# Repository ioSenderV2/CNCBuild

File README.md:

# CNCBuild

The machine, and everything about building, wiring, configuring and instrumenting it. Gantry beams are
**stacked pairs of 8020 `30-6060`** on HGR20 rails and 1605 ball screws.

Written down because these facts kept getting re-derived in conversation - travels, plate dimensions,
what shares a drag chain, which stored setting disagreed with the machine. A firmware fork's scratch
folder was the wrong home for them. The project's history at milestone level is
[TIMELINE.md](TIMELINE.md).

| Folder | What is in it |
|---|---|
| [`machine/`](machine) | The build itself: extrusions, rails, screws, plates, and the mechanical decisions with their reasons |
| [`linear-encoder/`](linear-encoder) | Magnetic linear scales + AS5311 + ESP32-S3 → CAN → grblHAL. The most developed subsystem; design complete, nothing built |
| [`commissioning/`](commissioning) | Measurements taken **from the machine** - travels, squaring, tape extents. The authority when the config disagrees |
| [`wiring/`](wiring) | How the boxes connect - the DB37 between the controller box and the remote axis breakout box |

## Generated views - regenerate, never edit

Three files are built from the prose rather than maintained beside it, because a
hand-maintained summary drifts from what it summarises. That is not hypothetical here: on
2026-10-02 two settled decisions were relitigated, both because a pointer had gone stale.

| Build it with | What you get |
|---|---|
| **`tools\regen.ps1`** | **everything derived, in dependency order, ending with `CNC Build.zip`.** The registry check first, then VALUES/registry.html/fusion CSV, fasteners, the cut list, the 3D model, the shop pack tallies, STATUS and INDEX, the four checkers, then the PDFs - and `make-pdf` bundles the zip on a clean print. `-NoPdf` stops after the checkers and says plainly that the PDFs and the zip are then stale. **This is the one to run**; the rows below are what it calls |
| `python tools/status.py all` | [`STATUS.md`](STATUS.md) - every open item, harvested from the SETTLED: OPEN: FLAG: REJECTED: markers in the prose. [`INDEX.md`](INDEX.md) - every heading in the repo |
| `tools\make-pdf.ps1` | **`docs/build-document.pdf`** - the whole mechanical design as one printable file: the thirteen `machine/*.md` files in reading order, a clickable contents, all fifteen photographs embedded with their captions, and links into the shop pack. ~4.4 MB, 97 pages. **Untracked** - rebuild it, do not commit it |

**If a generated file and a `.md` file disagree, the `.md` file wins** and the generated copy
is stale. The PDF needs two packages - `python -m pip install markdown pillow` - the first to
render the prose, the second to scale the photographs to print size on the way in (22.9 MB of
originals become 4.4 MB of PDF, still over 300 dpi at the size they are printed; the originals
in `machine/photos/` are never touched). `status.py` is stdlib-only on purpose, because it
gates correctness and the PDF does not.

## What lives elsewhere

| | Where | Why |
|---|---|---|
| grblHAL firmware + the CAN plugin | `stevenrwood/iMXRT1062`, branch `srw/local-build-config` | It is firmware and needs that build tree |
| ioSender (the sender application) | `ioSenderV2/ioSender` | Its own product |

## A standing rule for this repo

**The machine is the authority, not the configuration.** `$130` once read 889 mm against a real 860 mm,
because a catalog preset overwrote a measured value - which quietly cost soft-limit protection until it
was found by accident. Anything in `commissioning/` is measured; anything quoted from a config file is
labelled as such.

Datasheets are **committed, not linked**. The ESP32 module's header pinout was extracted once, lost, and
had to be recovered from a schematic - and both of that vendor's URLs refuse a plain fetch. A link is not
a copy.

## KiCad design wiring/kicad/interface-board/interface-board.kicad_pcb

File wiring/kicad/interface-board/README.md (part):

# Interface board - KiCad

The termination board that replaces the DB37 breakout: machine cables in through the
enclosure lid, RP23U5XBB controller fed out the other side. All connectors, no actives -
the 12 V arrives regulated from **its own mains-fed 12 V supply**, on the fourth pair off
the E-stop contactor's block. See
[`../../cabinet-power-and-grounding.md`](../../cabinet-power-and-grounding.md).

> FLAG: **NOT a 36 V -> 12 V buck.** This line said so until 2026-11-05 and it was wrong
> in a way nothing on the board shows: a buck off the motor rail ties logic ground to the
> motor return and throws away the drives' measured per-signal isolation. The board's
> 12 V input connector does not care where the 12 V comes from, so **nothing ordered is
> affected** - only what gets wired into it.

| File | |
|---|---|
| `interface-board.kicad_sch` | The schematic. Symbols are **embedded** (`lib_symbols`), so it needs no external libraries. |
| `interface-board.kicad_pcb` | **REV C, this branch: 121 x 104.5 mm, FOUR layers** - same outline, stackup and corner M3 holes as Rev B (22,4 / 117.3,4 / 5,99.8 / 117.3,99.8 from the top-left; [`../../../docs/drawings/board-mounting.html`](../../../docs/drawings/board-mounting.html) is the drilling drawing). **Top half MACHINE IN, bottom half RP23 OUT; no 36 V on it.** Rev C adds the five alarm-OR jumpers, swaps 12 V OUT and the UART1 header, and renames SPIN_PWM - the Rev C section below is the record. **The rev-b branch holds Rev B as ordered; main still holds Rev A** (210 x 94, 2 layers) - the boards in hand. |
| `interface-board.pretty/` | Project footprints for the two parts KiCad's libraries lack: the 85508 jack and the 3P single-row header, both taken from the committed Molex drawings. |
| `route.py` | Regenerates ALL copper from the placed footprints - the Rev B rewrite of the channel router. Owns every track on the board; re-run it after moving a part, then refill zones via the DRC command below. GND and +12V are inner-plane zones and route themselves (every pad on both nets is through-hole); signals run as F.Cu verticals into packed B.Cu lane corridors. **Finds the board beside itself** - it carried a hard-coded Windows path until 2026-11-14 and now runs from either machine. Verticals cross a connector row on searched columns, 0.70 mm apart - track-past-via, not just track-track - with jogs in the gap above the row. |
| `fab/oshpark/` | Manufacturing outputs for **OSH Park**: gerbers (Protel extensions), Excellon drill, and `interface-board-oshpark.zip` - the one file their upload takes. Board is 210 x 94, 2 layers; their standard 1.6 mm matches the 85508 jack's 1.57 tooling. **Rev A ordered 2026-11-03**, OSH Park order xPBWS3rt, $164.95 for 3 with FedEx 2 Day - this zip is what was uploaded; the order is recorded in [`orders/`](../../../orders/README.md), where the invoice PDF is kept out of git. Regenerate after any board change with the two kicad-cli export commands, then re-zip. |
| `fab/oshpark-revc/` | **Rev C quote package - built 2026-11-26, NOT ordered.** `interface-board-revc-oshpark.zip`, 13 files, same layer set and framing as Rev B's package; regenerate with `make-fab-revc.ps1`. |
| `make-fab-revc.ps1` | Builds the Rev C quote package - DRC with refill and parity first, refuses to build if it is not clean, keeps the drill map out of the zip. |
| `rev-c-changes.py` | **The Rev C one-shot, 2026-11-26**: J19 to a row-B terminal block, J37 stood up in row A, the SPIN_0_10V rename, and JP1-JP5 placed. Refuses a board that already carries JP1. Kept as the record, including the three jumper placements that failed routing and why. |
| `fab/oshpark-revb/` | **Rev B manufacturing outputs - ORDERED 2026-11-15**, OSH Park order G6Jj6s46, 3 boards on Four Layer Super Swift, $429.80 with UPS Next Day Air - this zip is what was uploaded; the order is recorded in [`orders/`](../../../orders/README.md), invoice kept out of git. `interface-board-revb-oshpark.zip` is the single file their upload takes: 13 files, all four copper layers (`.gtl` `.g1` `.g2` `.gbl`), masks, silks, `.gm1` outline and the Excellon drill. The drill **map** is written alongside but deliberately kept **out of the zip** - it is a `.gbr` and their uploader can mistake it for a copper layer. Outline read from the plotted gerber: **x 5..126 by y 5..109.5 - 121.00 x 104.50 mm, 19.6 sq in.** Regenerate after any board change **with `make-fab-revb.ps1`**, which keeps the refill and the map-exclusion from being forgotten. **Rev A's order record in `fab/oshpark/` is not touched by this.** |
| `silk.py` | Regenerates every free silkscreen label (function names, per-terminal signal names). Owns all board text - edit its tables, not the board. |
| `interface-board.kicad_pro` | Project wrapper. |
| `netlist.txt` | The connection list. **Generated from the routed board by `make-netlist.py`** - not hand-kept, and not from the seed. |
| `make-netlist.py` | Writes `netlist.txt` from the board. Run after any net change. |
| `interface-board-bom.csv` | **Generated** - kicad-cli sch export bom, one row per part with its board function as the value. Regenerate after any schematic change; the sensor and controller boards carry the same file beside their schematics. |
| `rev-a-validation.md` | The meter checkout for the three **Rev A** boards in hand - footprint fit, bridge sweep, net-by-net continuity against the Rev A netlist, jack-face map, first 12 V. Run it before the board meets the RP23. Its tables are from **main's** routed board, not this branch's. |
| `make-fab-revb.ps1` | Builds the whole Rev B quote package - DRC with refill, both exports, the zip. Refuses to build if DRC is not clean. Run this rather than the export commands by hand. |
| `swap-power-connectors.py` | Placed the three cabinet power feeds as Mini-Fit Jr. Kept because it carries the courtyard arithmetic for row A, which is the tightest row on the board. The 36 V one of the three has since gone. |
| `make-mech.py` | **The board as mechanical drawings, 2026-11-14**, for laying out the enclosure in Fusion. Writes `mech/interface-board-revc.dxf` (Rev C names since 2026-11-26) - perimeter, the four mounting holes at drilled diameter, and one rectangle per connector, on separate layers (`BOARD`, `HOLES`, `BODY_TOP`, `BODY_BOTTOM`, plus `FAB_DETAIL`, `COURTYARD` and `REFS` for reference). Millimetres, origin at the board's bottom-left corner, y up, seen from the component side. **The rectangles are the headers on the board - the mating plugs are bigger.** Also writes `mech/interface-board-revc.step`, untracked: the board with its connectors standing on it. The Molex bodies appear only on a machine that has the untracked `manufacturer-assets/3d/` downloads; the terminal blocks have no model anywhere. |
| `attach-models.py` | **Molex's own 3D models on the Molex connectors, 2026-11-14** - the RJ45 jacks and all three Mini-Fit Jr headers, which KiCad ships nothing for. The four STEP files are his download and sit **untracked** in `manufacturer-assets/3d/`; a clone without them still opens and passes DRC, and just lacks those parts in 3D. Each model was aligned by slicing it under the housing and matching its pins and pegs to the footprint's holes, then checked by exporting one connector alone and measuring where it landed. Re-runnable. |
| `add-fan-headers.py` | **The two fan headers, 2026-11-14**: adds J60 and J61 to the schematic and the board and slides 12 V OUT 0.4 mm west. One-shot - it refuses a board that already has J60. Kept as the record, with the two placements that were tried first and why they failed. |
| `remove-36v.py` | **The strip-down, 2026-11-14**: took J50-J55 and both 36 V nets off the schematic and the board, moved everything under the limit row up 27.5 mm, brought the east mounting holes in and redrew the outline. One-shot - it refuses a board with no J50. Kept as the record. |
| `generate.py` | **The seed that produced the first version - not the live source once KiCad has touched the file.** See the warning below. |

> FLAG: **`generate.py` is a SEED, not the source of truth once the schematic has been
> opened and re-saved by KiCad.** Re-running it overwrites hand edits and layout work.
> Same rule as the two linear-encoder boards. If the design changes, edit in Eeschema.
>
> FLAG: **AND `netlist.txt` IS NO LONGER ITS OUTPUT.** It used to be, which meant the
> only way to refresh the netlist was to run the seed - which would have destroyed the
> board. So it was hand-edited instead, and had already lost its trailer that way.
> `make-netlist.py` now derives it from the routed board, and
> `drc --schematic-parity` is what makes "from the board" and "from the schematic" the
> same statement.

## What is on it

| Machine side (top-entry, through the lid) | Controller side |
|---|---|
| 5x RJ45 vertical, one cat6 per stepper - column order **X, Y1, Y2, Z, B**, each with its limit 3P stacked below it | 2x10 IDC ribbon to RP23 **J20** (pin-for-pin), middle of row A |
| Mini-Fit Jr 3P - 3D probe (12 V), 3P - toolsetter (12 V) | 2x3 IDC ribbon to RP23 **J24** servo alarms, west end of row A |
| 2x Mini-Fit Jr 2P - touch probes | Mini-Fit Jr 2P - 12 V IN (latched, so a pulled feed has no bare conductor); **12 V OUT is a 3.5 mm 2P TB on the bottom edge since Rev C**, +12V / G on its silk |
| 2x Mini-Fit Jr 2P - mist, flood | 3.5 mm TBs, one position per signal with silk names: limits 5P, VFD 4P (EN / G / G / 0-10V), probe + door 2P |
| Mini-Fit Jr 4P - VFD (Enable, GND, GND, 0-10 V) | 3.5 mm TBs passing the new inputs through: mist 2P, flood 2P, control 4P; UART1 leaves on a **1x4 2.54 mm header standing at the east end of row A since Rev C** - dupont jumpers straight to the RP23's 4-pin UART header |
| **JP1-JP5 - the alarm wire-OR jumpers**, one per axis zone in X / Y / A / Z / B order: all five shunts fitted ties the five AL lines together and **J17 pin 1 is the one alarm out for a Teensy's single motor-fault input**; shunts off = five separate alarms on the ribbon, as the RP23 expects | |
| Mini-Fit Jr 4P - cycle start / feed hold / e-stop / spare | 5x 2.54 mm header, **GND / Step / Dir / Enable** per axis - jumper to a Teensy T41U5XBB instead of the ribbon |
| Mini-Fit Jr 4P - UART1 for CAN, **TX / RX / 3.3V / GND** | |
| **4-pin fan header - RAD FAN (J60)**, always-on 12 V: the external fan on the coolant radiator. In the top half, under the Z column, because its lead comes in through the lid like a machine cable | **4-pin fan header - CASE FAN (J61)**, always-on 12 V: the 40 mm Noctua inside the case. East end of row A, beside the 12 V pair - its lead never leaves the enclosure |

**Y1 drives the controller's Y, Y2 drives A.** The three touch/3D probe signals are
wired-OR onto one PROBE net; the toolsetter goes to DOOR. Mist, flood, control and
UART1 pass straight through, connector to output terminal, position for position -
UART1's output being the 1x4 header rather than a screw block.

**RJ45 pin map** (striped conductor = signal, solid = return):
1 Step, 3 Enable, 5 Dir, 7 Alarm; evens GND. Step and Alarm sit on opposite edges of
the jack - Step is the aggressor and Alarm feeds EStop. Signals on odds is correct on
the twists by construction: in T568 every odd pin's twist partner is an even pin.

**"Evens GND" does not say WHICH even pin, and that is where a split pair comes from.**
The twists are **1-2, 3-6, 4-5, 7-8**. So each signal's return leg must land on its
own twist partner: Step 1-2, Enable **3-6**, Dir **5-4**, Alarm 7-8. Wiring it as the
numbers read - 3 with 4, 5 with 6 - puts Enable and Dir in each other's twists. The
board cannot catch it, because all four evens are the same GND net: it passes
continuity and works, and costs only signal integrity. Drive-end terminals and the
reasoning are in [`../../hbt57112c-drives.md`](../../hbt57112c-drives.md).

**3P pin order**: 1 = 12 V, 2 = signal, 3 = GND - matches the SN04's brown/black/blue.

**The two fan headers - his, 2026-11-14.** Standard 4-pin PC fan headers, keyed, taking a
3-pin or a 4-pin plug: **pin 1 GND, pin 2 +12 V, pin 3 tach and pin 4 PWM not connected.**
**Both are always on** - the board has no actives, so nothing here switches or reads a fan,
and a PWM fan with pin 4 open runs at full speed. They run whenever the 12 V supply is up,
which includes through an e-stop. Both pins are the inner planes, so the headers took no
routing. **The case fan's pin 1 is at the BOTTOM of its header and the radiator fan's is at
the TOP** - the key on the housing is what matters, not the position. The fans come off the
12 V supply's budget: the MDR is 40 W, 3.3 A, and a 40 mm Noctua is about 0.05 A - the
radiator fan's draw is whatever that fan's label says, and it has not been read.
[`add-fan-headers.py`](add-fan-headers.py) is the record of how they went on.

🔴 **THERE IS NO 36 V ON THIS BOARD - his, 2026-11-14.** Stepper power is distributed on
the DIN rail beside the supply, on Phoenix PT 4-QUATTRO blocks, and the 18/2 motor supply
cables land there. This board carries logic and 12 V only. Three things decided it, in the
order they turned up:

- **The supply grew to 26.6 A** (XDR-960-36) under pours sized for 16.5.
- **The input connector could never carry it.** Molex PS-5556-001 table 3: a 4-circuit
  Mini-Fit Jr is **8 A per circuit** on 16 or 18 AWG with brass terminals, 7 A with phosphor
  bronze - so the doubled legs were 16 A, not the 18 this file claimed. And drawing
  55660021-SD note 10: **"parts are not designed for current sharing"**, which is what
  doubling a leg is.
- **45 cm2 of 36 V pour sat 0.2 mm over the logic planes** - roughly 0.9 nF between the
  motor bus and logic ground, calculated not measured, on a board whose whole point is
  keeping the two apart.

The rule the pours were built around still stands, and is now kept by absence: **the motor
return is not a ground and never meets logic GND on this board.**

**THIS BOARD HAS NO PE CONNECTION AT ALL, AND THAT IS DELIBERATE.** There is no earth
or chassis net on it - 42 nets and four named no-connects, none of them PE - **all four mounting holes are
unplated NPTH with no net**, and its enclosure is 3D printed, so there is no chassis
to bond. **Its GND arrives on one pad, J18.2 of the 12 V IN connector**, and leaves on
J19.2 to the RP23. The In1 plane distributes it from there.

✅ **THE TWO RULES ARE THE SAME RULE: SEPARATE EVERYWHERE, JOINED AT ONE POINT.** Logic
GND and the 36 V return do meet - **back at the cabinet's PE bar**, which carries
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
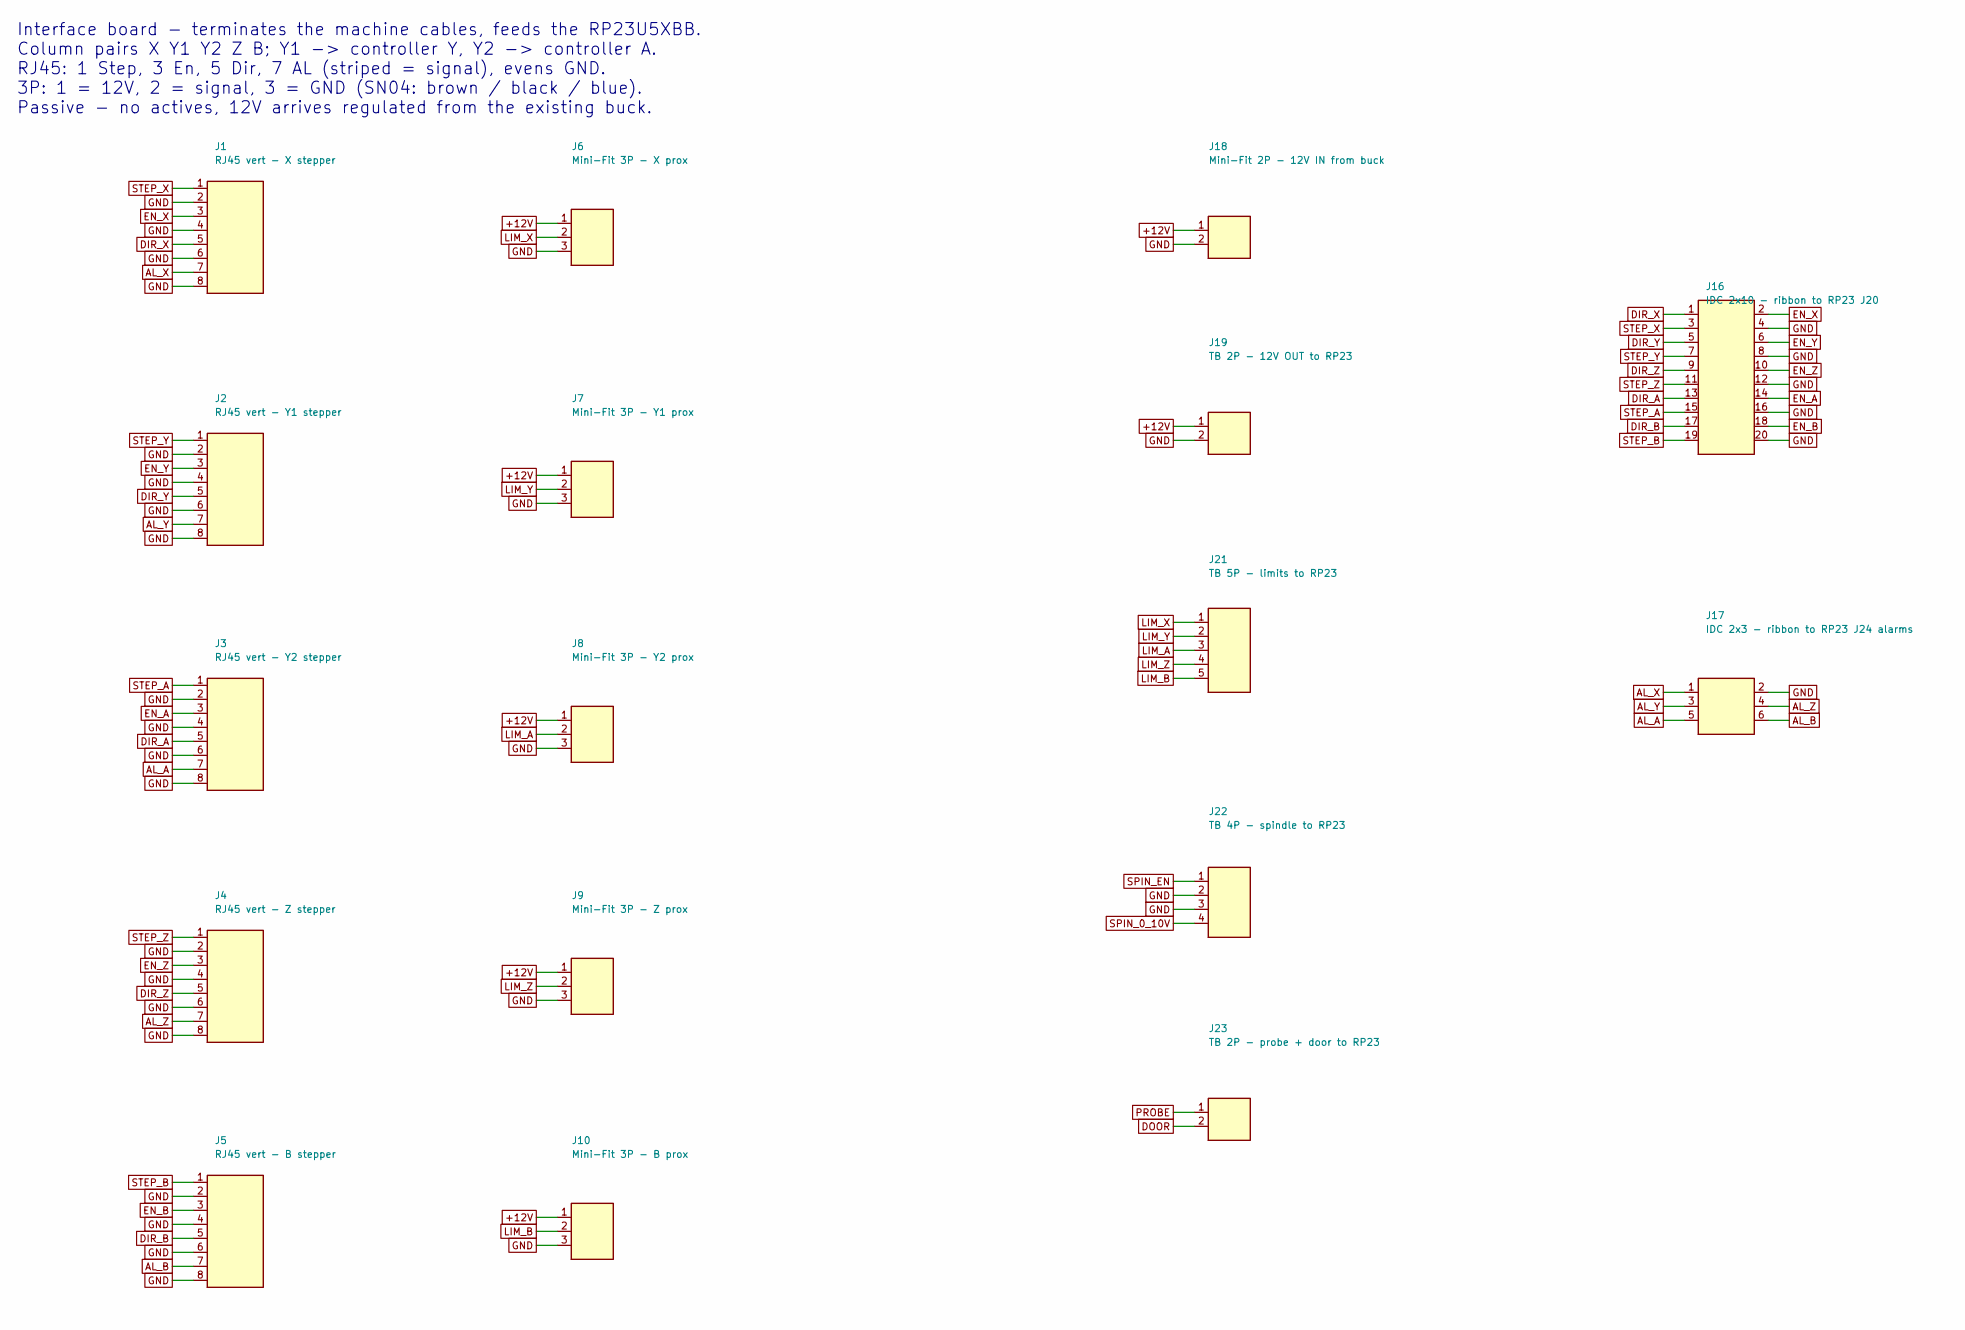
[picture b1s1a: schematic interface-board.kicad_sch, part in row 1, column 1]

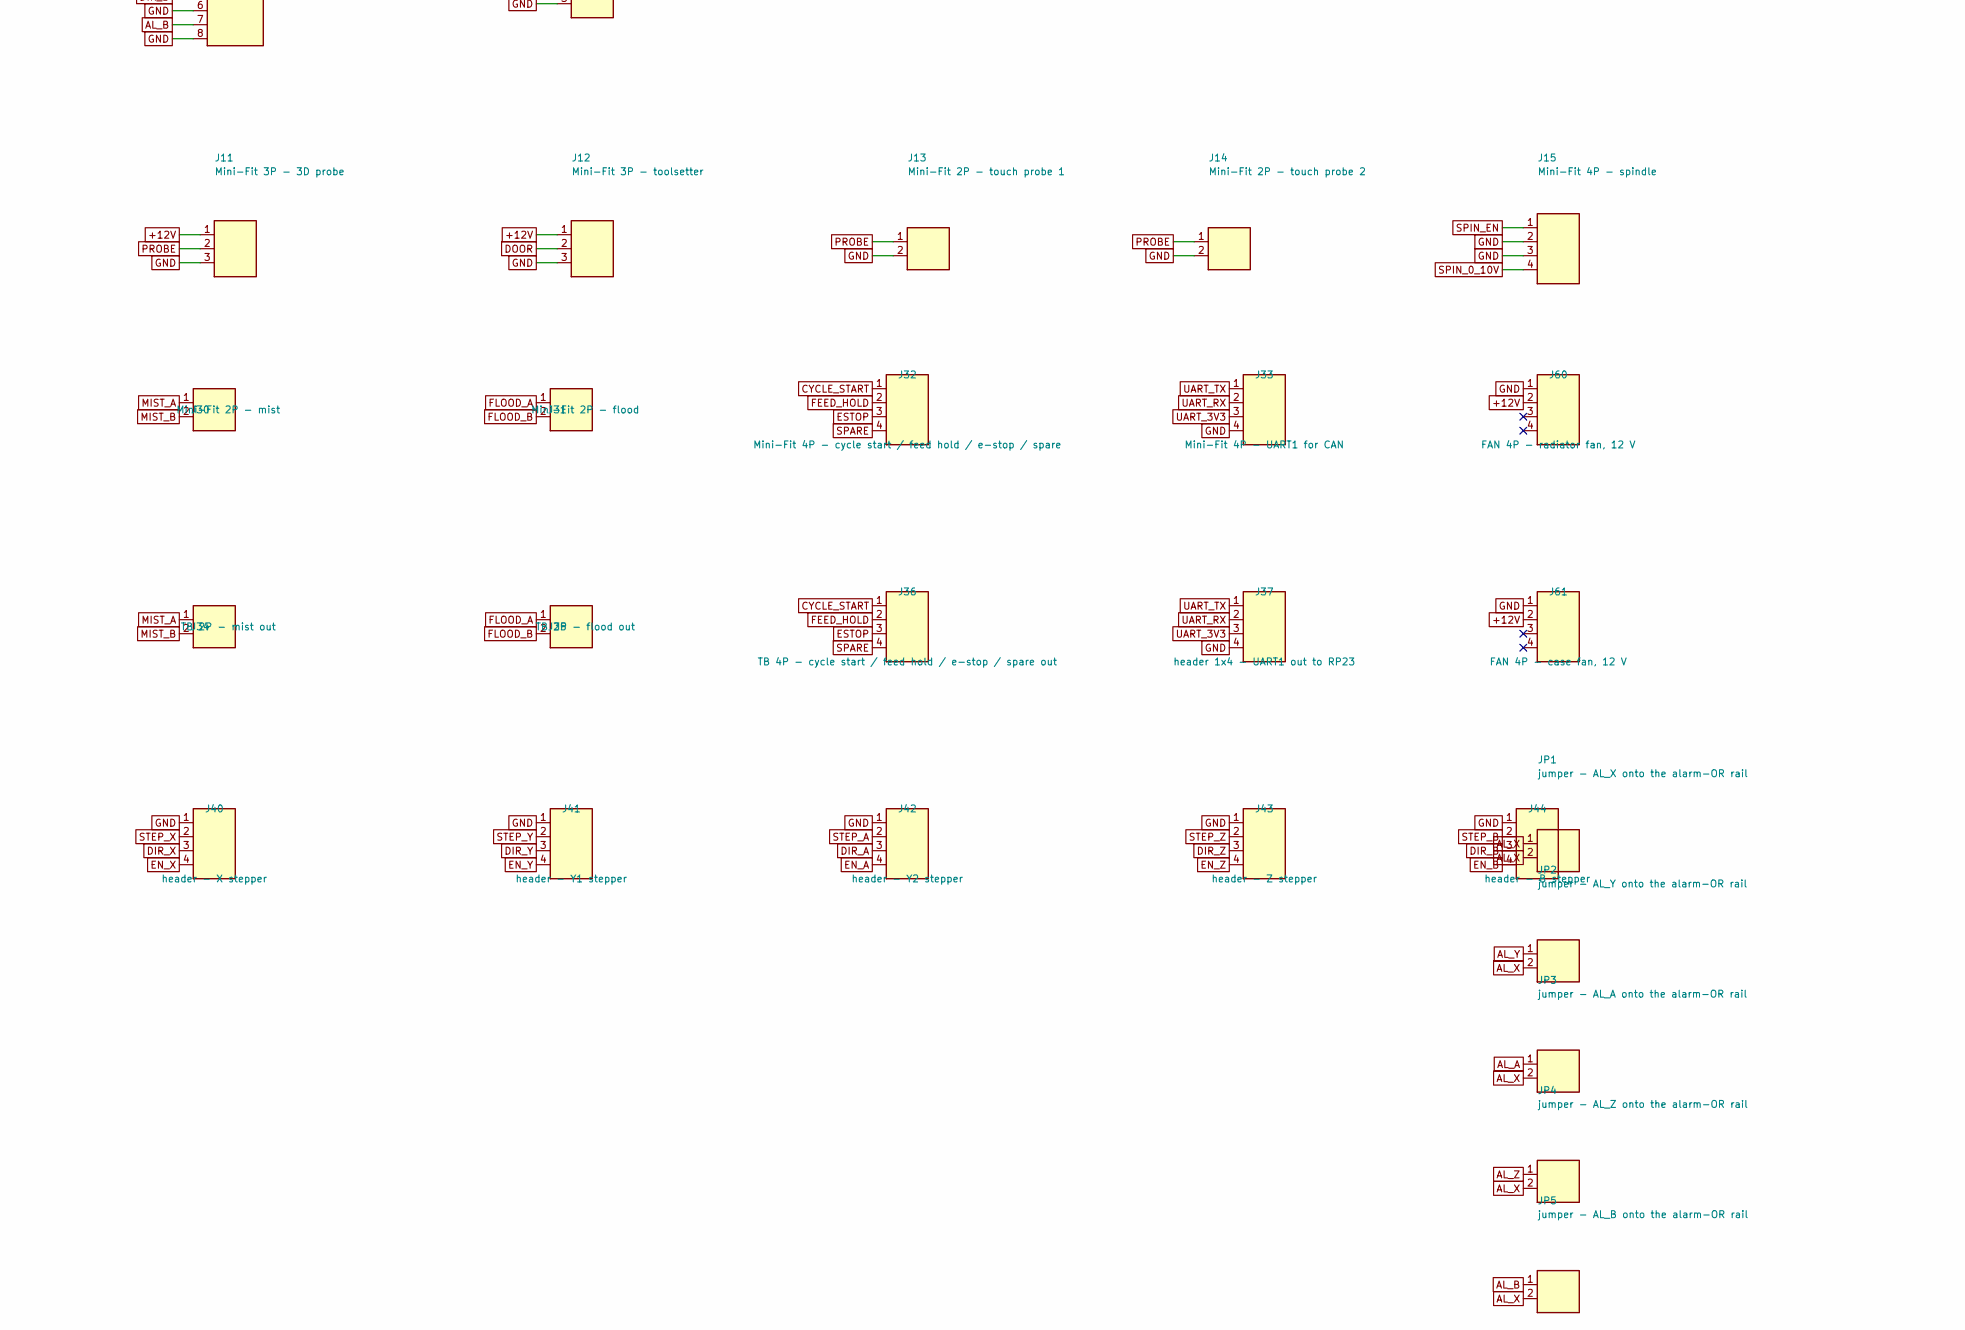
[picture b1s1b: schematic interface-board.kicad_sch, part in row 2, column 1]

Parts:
J1: RJ45 vert - X stepper; RJ45_Molex_85508-5001_Vertical
J2: RJ45 vert - Y1 stepper; RJ45_Molex_85508-5001_Vertical
J3: RJ45 vert - Y2 stepper; RJ45_Molex_85508-5001_Vertical
J4: RJ45 vert - Z stepper; RJ45_Molex_85508-5001_Vertical
J5: RJ45 vert - B stepper; RJ45_Molex_85508-5001_Vertical
J6: Mini-Fit 3P - X prox; Molex_Mini-Fit_Jr_5566-03A3_1x03_P4.20mm_Vertical
J7: Mini-Fit 3P - Y1 prox; Molex_Mini-Fit_Jr_5566-03A3_1x03_P4.20mm_Vertical
J8: Mini-Fit 3P - Y2 prox; Molex_Mini-Fit_Jr_5566-03A3_1x03_P4.20mm_Vertical
J9: Mini-Fit 3P - Z prox; Molex_Mini-Fit_Jr_5566-03A3_1x03_P4.20mm_Vertical
J10: Mini-Fit 3P - B prox; Molex_Mini-Fit_Jr_5566-03A3_1x03_P4.20mm_Vertical
J11: Mini-Fit 3P - 3D probe; Molex_Mini-Fit_Jr_5566-03A3_1x03_P4.20mm_Vertical
J12: Mini-Fit 3P - toolsetter; Molex_Mini-Fit_Jr_5566-03A3_1x03_P4.20mm_Vertical
J13: Mini-Fit 2P - touch probe 1; Molex_Mini-Fit_Jr_5566-02A2_2x01_P4.20mm_Vertical
J14: Mini-Fit 2P - touch probe 2; Molex_Mini-Fit_Jr_5566-02A2_2x01_P4.20mm_Vertical
J15: Mini-Fit 4P - spindle; Molex_Mini-Fit_Jr_5566-04A2_2x02_P4.20mm_Vertical
J16: IDC 2x10 - ribbon to RP23 J20; IDC-Header_2x10_P2.54mm_Vertical
J17: IDC 2x3 - ribbon to RP23 J24 alarms; IDC-Header_2x03_P2.54mm_Vertical
J18: Mini-Fit 2P - 12V IN from buck; Molex_Mini-Fit_Jr_5566-02A2_2x01_P4.20mm_Vertical
J19: TB 2P - 12V OUT to RP23; TerminalBlock_4Ucon_1x02_P3.50mm_Horizontal
J21: TB 5P - limits to RP23; TerminalBlock_4Ucon_1x05_P3.50mm_Horizontal
J22: TB 4P - spindle to RP23; TerminalBlock_4Ucon_1x04_P3.50mm_Horizontal
J23: TB 2P - probe + door to RP23; TerminalBlock_4Ucon_1x02_P3.50mm_Horizontal
J30: Mini-Fit 2P - mist; Molex_Mini-Fit_Jr_5566-02A2_2x01_P4.20mm_Vertical
J31: Mini-Fit 2P - flood; Molex_Mini-Fit_Jr_5566-02A2_2x01_P4.20mm_Vertical
J32: Mini-Fit 4P - cycle start / feed hold / e-stop / 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; Molex_Mini-Fit_Jr_5566-04A2_2x02_P4.20mm_Vertical
J33: Mini-Fit 4P - UART1 for CAN; Molex_Mini-Fit_Jr_5566-04A2_2x02_P4.20mm_Vertical
J34: TB 2P - mist out; TerminalBlock_4Ucon_1x02_P3.50mm_Horizontal
J35: TB 2P - flood out; TerminalBlock_4Ucon_1x02_P3.50mm_Horizontal
J36: TB 4P - cycle start / feed hold / e-stop / spare 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; TerminalBlock_4Ucon_1x04_P3.50mm_Horizontal
J37: header 1x4 - UART1 out to RP23; PinHeader_1x04_P2.54mm_Vertical
J40: header - X stepper; PinHeader_1x04_P2.54mm_Vertical
J41: header - Y1 stepper; PinHeader_1x04_P2.54mm_Vertical
J42: header - Y2 stepper; PinHeader_1x04_P2.54mm_Vertical
J43: header - Z stepper; PinHeader_1x04_P2.54mm_Vertical
J44: header - B stepper; PinHeader_1x04_P2.54mm_Vertical
J60: FAN 4P - radiator fan, 12 V; FanPinHeader_1x04_P2.54mm_Vertical
J61: FAN 4P - case fan, 12 V; FanPinHeader_1x04_P2.54mm_Vertical
JP1: jumper - AL_X onto the alarm-OR rail; PinHeader_1x02_P2.54mm_Vertical
JP2: jumper - AL_Y onto the alarm-OR rail; PinHeader_1x02_P2.54mm_Vertical
JP3: jumper - AL_A onto the alarm-OR rail; PinHeader_1x02_P2.54mm_Vertical
JP4: jumper - AL_Z onto the alarm-OR rail; PinHeader_1x02_P2.54mm_Vertical
JP5: jumper - AL_B onto the alarm-OR rail; PinHeader_1x02_P2.54mm_Vertical

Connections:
+12V: J6.1, J7.1, J8.1, J9.1, J10.1, J11.1, J12.1, J18.1, J19.1, J60.2, J61.2
AL_A: J3.7, J17.5, JP3.1
AL_B: J5.7, J17.6, JP5.1
AL_X: J1.7, J17.1, JP1.1, JP1.2, JP2.2, JP3.2, JP4.2, JP5.2
AL_Y: J2.7, J17.3, JP2.1
AL_Z: J4.7, J17.4, JP4.1
CYCLE_START: J32.1, J36.1
DIR_A: J3.5, J16.13, J42.3
DIR_B: J5.5, J16.17, J44.3
DIR_X: J1.5, J16.1, J40.3
DIR_Y: J2.5, J16.5, J41.3
DIR_Z: J4.5, J16.9, J43.3
DOOR: J12.2, J23.2
EN_A: J3.3, J16.14, J42.4
EN_B: J5.3, J16.18, J44.4
EN_X: J1.3, J16.2, J40.4
EN_Y: J2.3, J16.6, J41.4
EN_Z: J4.3, J16.10, J43.4
ESTOP: J32.3, J36.3
FEED_HOLD: J32.2, J36.2
FLOOD_A: J31.1, J35.1
FLOOD_B: J31.2, J35.2
GND: J1.2, J1.4, J1.6, J1.8, J2.2, J2.4, J2.6, J2.8, J3.2, J3.4, J3.6, J3.8, J4.2, J4.4, J4.6, J4.8, J5.2, J5.4, J5.6, J5.8, J6.3, J7.3, J8.3, J9.3, J10.3, J11.3, J12.3, J13.2, J14.2, J15.2, J15.3, J16.4, J16.8, J16.12, J16.16, J16.20, J17.2, J18.2, J19.2, J22.2, J22.3, J33.4, J37.4, J40.1, J41.1, J42.1, J43.1, J44.1, J60.1, J61.1
LIM_A: J8.2, J21.3
LIM_B: J10.2, J21.5
LIM_X: J6.2, J21.1
LIM_Y: J7.2, J21.2
LIM_Z: J9.2, J21.4
MIST_A: J30.1, J34.1
MIST_B: J30.2, J34.2
PROBE: J11.2, J13.1, J14.1, J23.1
SPARE: J32.4, J36.4
SPIN_0_10V: J15.4, J22.4
SPIN_EN: J15.1, J22.1
STEP_A: J3.1, J16.15, J42.2
STEP_B: J5.1, J16.19, J44.2
STEP_X: J1.1, J16.3, J40.2
STEP_Y: J2.1, J16.7, J41.2
STEP_Z: J4.1, J16.11, J43.2
UART_3V3: J33.3, J37.3
UART_RX: J33.2, J37.2
UART_TX: J33.1, J37.1

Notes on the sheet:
Interface board - terminates the machine cables, feeds the RP23U5XBB. Column pairs X Y1 Y2 Z B; Y1 -> controller Y, Y2 -> controller A. RJ45: 1 Step, 3 En, 5 Dir, 7 AL (striped = signal), evens GND. 3P: 1 = 12V, 2 = signal, 3 = GND (SN04: brown / black / blue). Passive - no actives, 12V arrives reg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

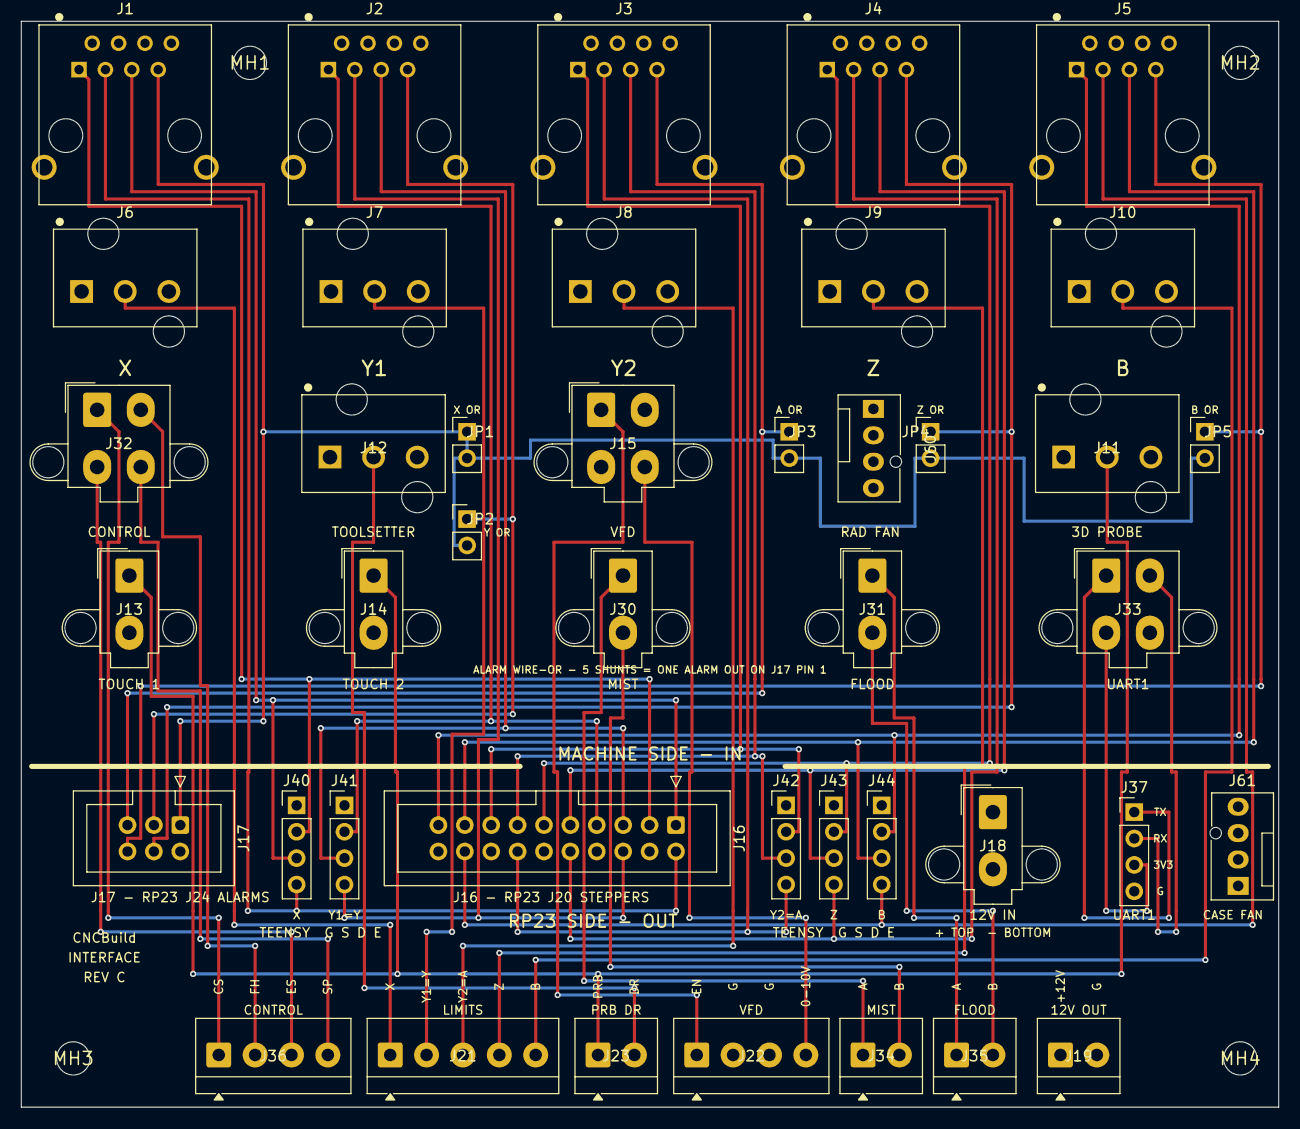
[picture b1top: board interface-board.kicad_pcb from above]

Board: 4 copper layers, 121.0 x 104.5 mm, 46 parts (0 on the bottom side), 42 nets.

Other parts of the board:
MH1, MH2, MH3, MH4: MountingHole_3.2mm

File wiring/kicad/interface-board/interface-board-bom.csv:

"Refs","Value","Footprint","Qty","DNP"
"J1","RJ45 vert - X stepper","interface-board:RJ45_Molex_85508-5001_Vertical","1",""
"J2","RJ45 vert - Y1 stepper","interface-board:RJ45_Molex_85508-5001_Vertical","1",""
"J3","RJ45 vert - Y2 stepper","interface-board:RJ45_Molex_85508-5001_Vertical","1",""
"J4","RJ45 vert - Z stepper","interface-board:RJ45_Molex_85508-5001_Vertical","1",""
"J5","RJ45 vert - B stepper","interface-board:RJ45_Molex_85508-5001_Vertical","1",""
"J6","Mini-Fit 3P - X prox","interface-board:Molex_Mini-Fit_Jr_5566-03A3_1x03_P4.20mm_Vertical","1",""
"J7","Mini-Fit 3P - Y1 prox","interface-board:Molex_Mini-Fit_Jr_5566-03A3_1x03_P4.20mm_Vertical","1",""
"J8","Mini-Fit 3P - Y2 prox","interface-board:Molex_Mini-Fit_Jr_5566-03A3_1x03_P4.20mm_Vertical","1",""
"J9","Mini-Fit 3P - Z prox","interface-board:Molex_Mini-Fit_Jr_5566-03A3_1x03_P4.20mm_Vertical","1",""
"J10","Mini-Fit 3P - B prox","interface-board:Molex_Mini-Fit_Jr_5566-03A3_1x03_P4.20mm_Vertical","1",""
"J11","Mini-Fit 3P - 3D probe","interface-board:Molex_Mini-Fit_Jr_5566-03A3_1x03_P4.20mm_Vertical","1",""
"J12","Mini-Fit 3P - toolsetter","interface-board:Molex_Mini-Fit_Jr_5566-03A3_1x03_P4.20mm_Vertical","1",""
"J13","Mini-Fit 2P - touch probe 1","Connector_Molex:Molex_Mini-Fit_Jr_5566-02A2_2x01_P4.20mm_Vertical","1",""
"J14","Mini-Fit 2P - touch probe 2","Connector_Molex:Molex_Mini-Fit_Jr_5566-02A2_2x01_P4.20mm_Vertical","1",""
"J15","Mini-Fit 4P - spindle","Connector_Molex:Molex_Mini-Fit_Jr_5566-04A2_2x02_P4.20mm_Vertical","1",""
"J16","IDC 2x10 - ribbon to RP23 J20","Connector_IDC:IDC-Header_2x10_P2.54mm_Vertical","1",""
"J17","IDC 2x3 - ribbon to RP23 J24 alarms","Connector_IDC:IDC-Header_2x03_P2.54mm_Vertical","1",""
"J18","Mini-Fit 2P - 12V IN from buck","Connector_Molex:Molex_Mini-Fit_Jr_5566-02A2_2x01_P4.20mm_Vertical","1",""
"J19","TB 2P - 12V OUT to RP23","TerminalBlock_4Ucon:TerminalBlock_4Ucon_1x02_P3.50mm_Horizontal","1",""
"J21","TB 5P - limits to RP23","TerminalBlock_4Ucon:TerminalBlock_4Ucon_1x05_P3.50mm_Horizontal","1",""
"J22","TB 4P - spindle to RP23","TerminalBlock_4Ucon:TerminalBlock_4Ucon_1x04_P3.50mm_Horizontal","1",""
"J23","TB 2P - probe + door to RP23","TerminalBlock_4Ucon:TerminalBlock_4Ucon_1x02_P3.50mm_Horizontal","1",""
"J30","Mini-Fit 2P - mist","Connector_Molex:Molex_Mini-Fit_Jr_5566-02A2_2x01_P4.20mm_Vertical","1",""
"J31","Mini-Fit 2P - flood","Connector_Molex:Molex_Mini-Fit_Jr_5566-02A2_2x01_P4.20mm_Vertical","1",""
"J32","Mini-Fit 4P - cycle start / feed hold / e-stop / spare","Connector_Molex:Molex_Mini-Fit_Jr_5566-04A2_2x02_P4.20mm_Vertical","1",""
"J33","Mini-Fit 4P - UART1 for CAN","Connector_Molex:Molex_Mini-Fit_Jr_5566-04A2_2x02_P4.20mm_Vertical","1",""
"J34","TB 2P - mist out","TerminalBlock_4Ucon:TerminalBlock_4Ucon_1x02_P3.50mm_Horizontal","1",""
"J35","TB 2P - flood out","TerminalBlock_4Ucon:TerminalBlock_4Ucon_1x02_P3.50mm_Horizontal","1",""
"J36","TB 4P - cycle start / feed hold / e-stop / spare out","TerminalBlock_4Ucon:TerminalBlock_4Ucon_1x04_P3.50mm_Horizontal","1",""
"J37","header 1x4 - UART1 out to RP23","Connector_PinHeader_2.54mm:PinHeader_1x04_P2.54mm_Vertical","1",""
"J40","header - X stepper","Connector_PinHeader_2.54mm:PinHeader_1x04_P2.54mm_Vertical","1",""
"J41","header - Y1 stepper","Connector_PinHeader_2.54mm:PinHeader_1x04_P2.54mm_Vertical","1",""
"J42","header - Y2 stepper","Connector_PinHeader_2.54mm:PinHeader_1x04_P2.54mm_Vertical","1",""
"J43","header - Z stepper","Connector_PinHeader_2.54mm:PinHeader_1x04_P2.54mm_Vertical","1",""
"J44","header - B stepper","Connector_PinHeader_2.54mm:PinHeader_1x04_P2.54mm_Vertical","1",""
"J60","FAN 4P - radiator fan, 12 V","Connector:FanPinHeader_1x04_P2.54mm_Vertical","1",""
"J61","FAN 4P - case fan, 12 V","Connector:FanPinHeader_1x04_P2.54mm_Vertical","1",""
"JP1","jumper - AL_X onto the alarm-OR rail","Connector_PinHeader_2.54mm:PinHeader_1x02_P2.54mm_Vertical","1",""
"JP2","jumper - AL_Y onto the alarm-OR rail","Connector_PinHeader_2.54mm:PinHeader_1x02_P2.54mm_Vertical","1",""
"JP3","jumper - AL_A onto the alarm-OR rail","Connector_PinHeader_2.54mm:PinHeader_1x02_P2.54mm_Vertical","1",""
"JP4","jumper - AL_Z onto the alarm-OR rail","Connector_PinHeader_2.54mm:PinHeader_1x02_P2.54mm_Vertical","1",""
"JP5","jumper - AL_B onto the alarm-OR rail","Connector_PinHeader_2.54mm:PinHeader_1x02_P2.54mm_Vertical","1",""

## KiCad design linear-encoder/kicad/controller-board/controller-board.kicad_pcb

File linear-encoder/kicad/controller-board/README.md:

# Controller board - KiCad

Schematic for the daughter board described in [`../../controller-board.md`](../../controller-board.md).

| File | |
|---|---|
| `controller-board.kicad_sch` | The schematic. Symbols are **embedded** (`lib_symbols`), so it needs no external libraries. |
| `controller-board.kicad_pro` | Project wrapper. |
| `netlist.txt` | The connection list, generated from the same source as the schematic. |
| `generate.py` | **The seed that produced the first version - not the live source any more.** See the warning below before re-running it. |

> FLAG: **`generate.py` is now a SEED, not the source of truth.**
> The schematic has since been **opened and re-saved by KiCad 10**, which upgraded the file format and
> may carry hand edits and layout work. **Re-running `generate.py` overwrites all of that.** Treat the
> `.kicad_sch` as the live document from here on; keep `generate.py` only as the record of how the
> netlist was derived, and if the design changes, edit in Eeschema and update `netlist.txt` to match.

## Status: verified against KiCad 10.0.5

Opened and checked with `kicad-cli`, not just written and hoped for:

| Check | Result |
|---|---|
| Parses / loads | **Yes** - `kicad-cli sch erc` and `sch export netlist` both succeed |
| Netlist matches `netlist.txt` | **Exactly.** All 15 nets, 0 mismatches, no extra or missing nodes - re-checked after KiCad re-saved the file, so connectivity survived the format upgrade |
| ERC violations | **22**, all one warning type - see below |

Reproduce with:

```
kicad-cli sch erc --severity-all --output erc-report.txt controller-board.kicad_sch
kicad-cli sch export netlist --format kicadsexpr --output kicad-export.net controller-board.kicad_sch
```

### The 22 remaining warnings are expected

All are `lib_symbol_issues`: *"The current configuration does not include the symbol library 'cnc'"*.
The symbols are embedded in the file rather than coming from a configured library, so KiCad notes it.
Nothing is broken - and the warning is arguably useful, because those symbols **are** placeholders.

An earlier run had 134 violations. The other 112 were real and are fixed:

- **107 x `endpoint_off_grid`** - placement origins were not multiples of 1.27 mm, so every pin and
  stub sat off the connection grid. Connections still resolved, but off-grid endpoints can silently
  fail to connect once a human edits the sheet. `generate.py` now snaps origins.
- **5 x `pin_not_connected`** - header pins 2 (5V), 5/7 (UART) and 6/8 (USB), which are deliberately
  unused. Now carry `no_connect` markers, which turns an error into a recorded decision.

## How it is drawn

**Connections are by net label on a short stub at each pin**, not point-to-point wires - electrically
identical for netlist and ERC purposes, and far less error-prone to generate than routing 40-odd nets
by computed coordinates. It reads as a fan-out list rather than a picture of wires, which is what the
board actually is.

## Symbols are placeholders - swap before layout

`cnc:RJ45_8`, `cnc:HDR_2x10`, `cnc:R`, `cnc:C` are minimal rectangles with correct pin numbering:
enough to carry the netlist, not real parts. Before layout, replace them with manufacturer symbols and
footprints - in particular:

- the RJ45: **shielded, NO integrated magnetics** (see the warning at the top of `controller-board.md`);
- the 2x10 header: **2.00 mm pitch**, not 2.54 mm.

`J1..J4` are X, Y, A, Z in that order; `J5` is the header to the module's `P1`.

Expect a "no power source" ERC complaint once real power symbols are used - 3V3 arrives through a
passive header pin, which is honest for a daughter board. A `PWR_FLAG` on `+3V3` and `GND` settles it.

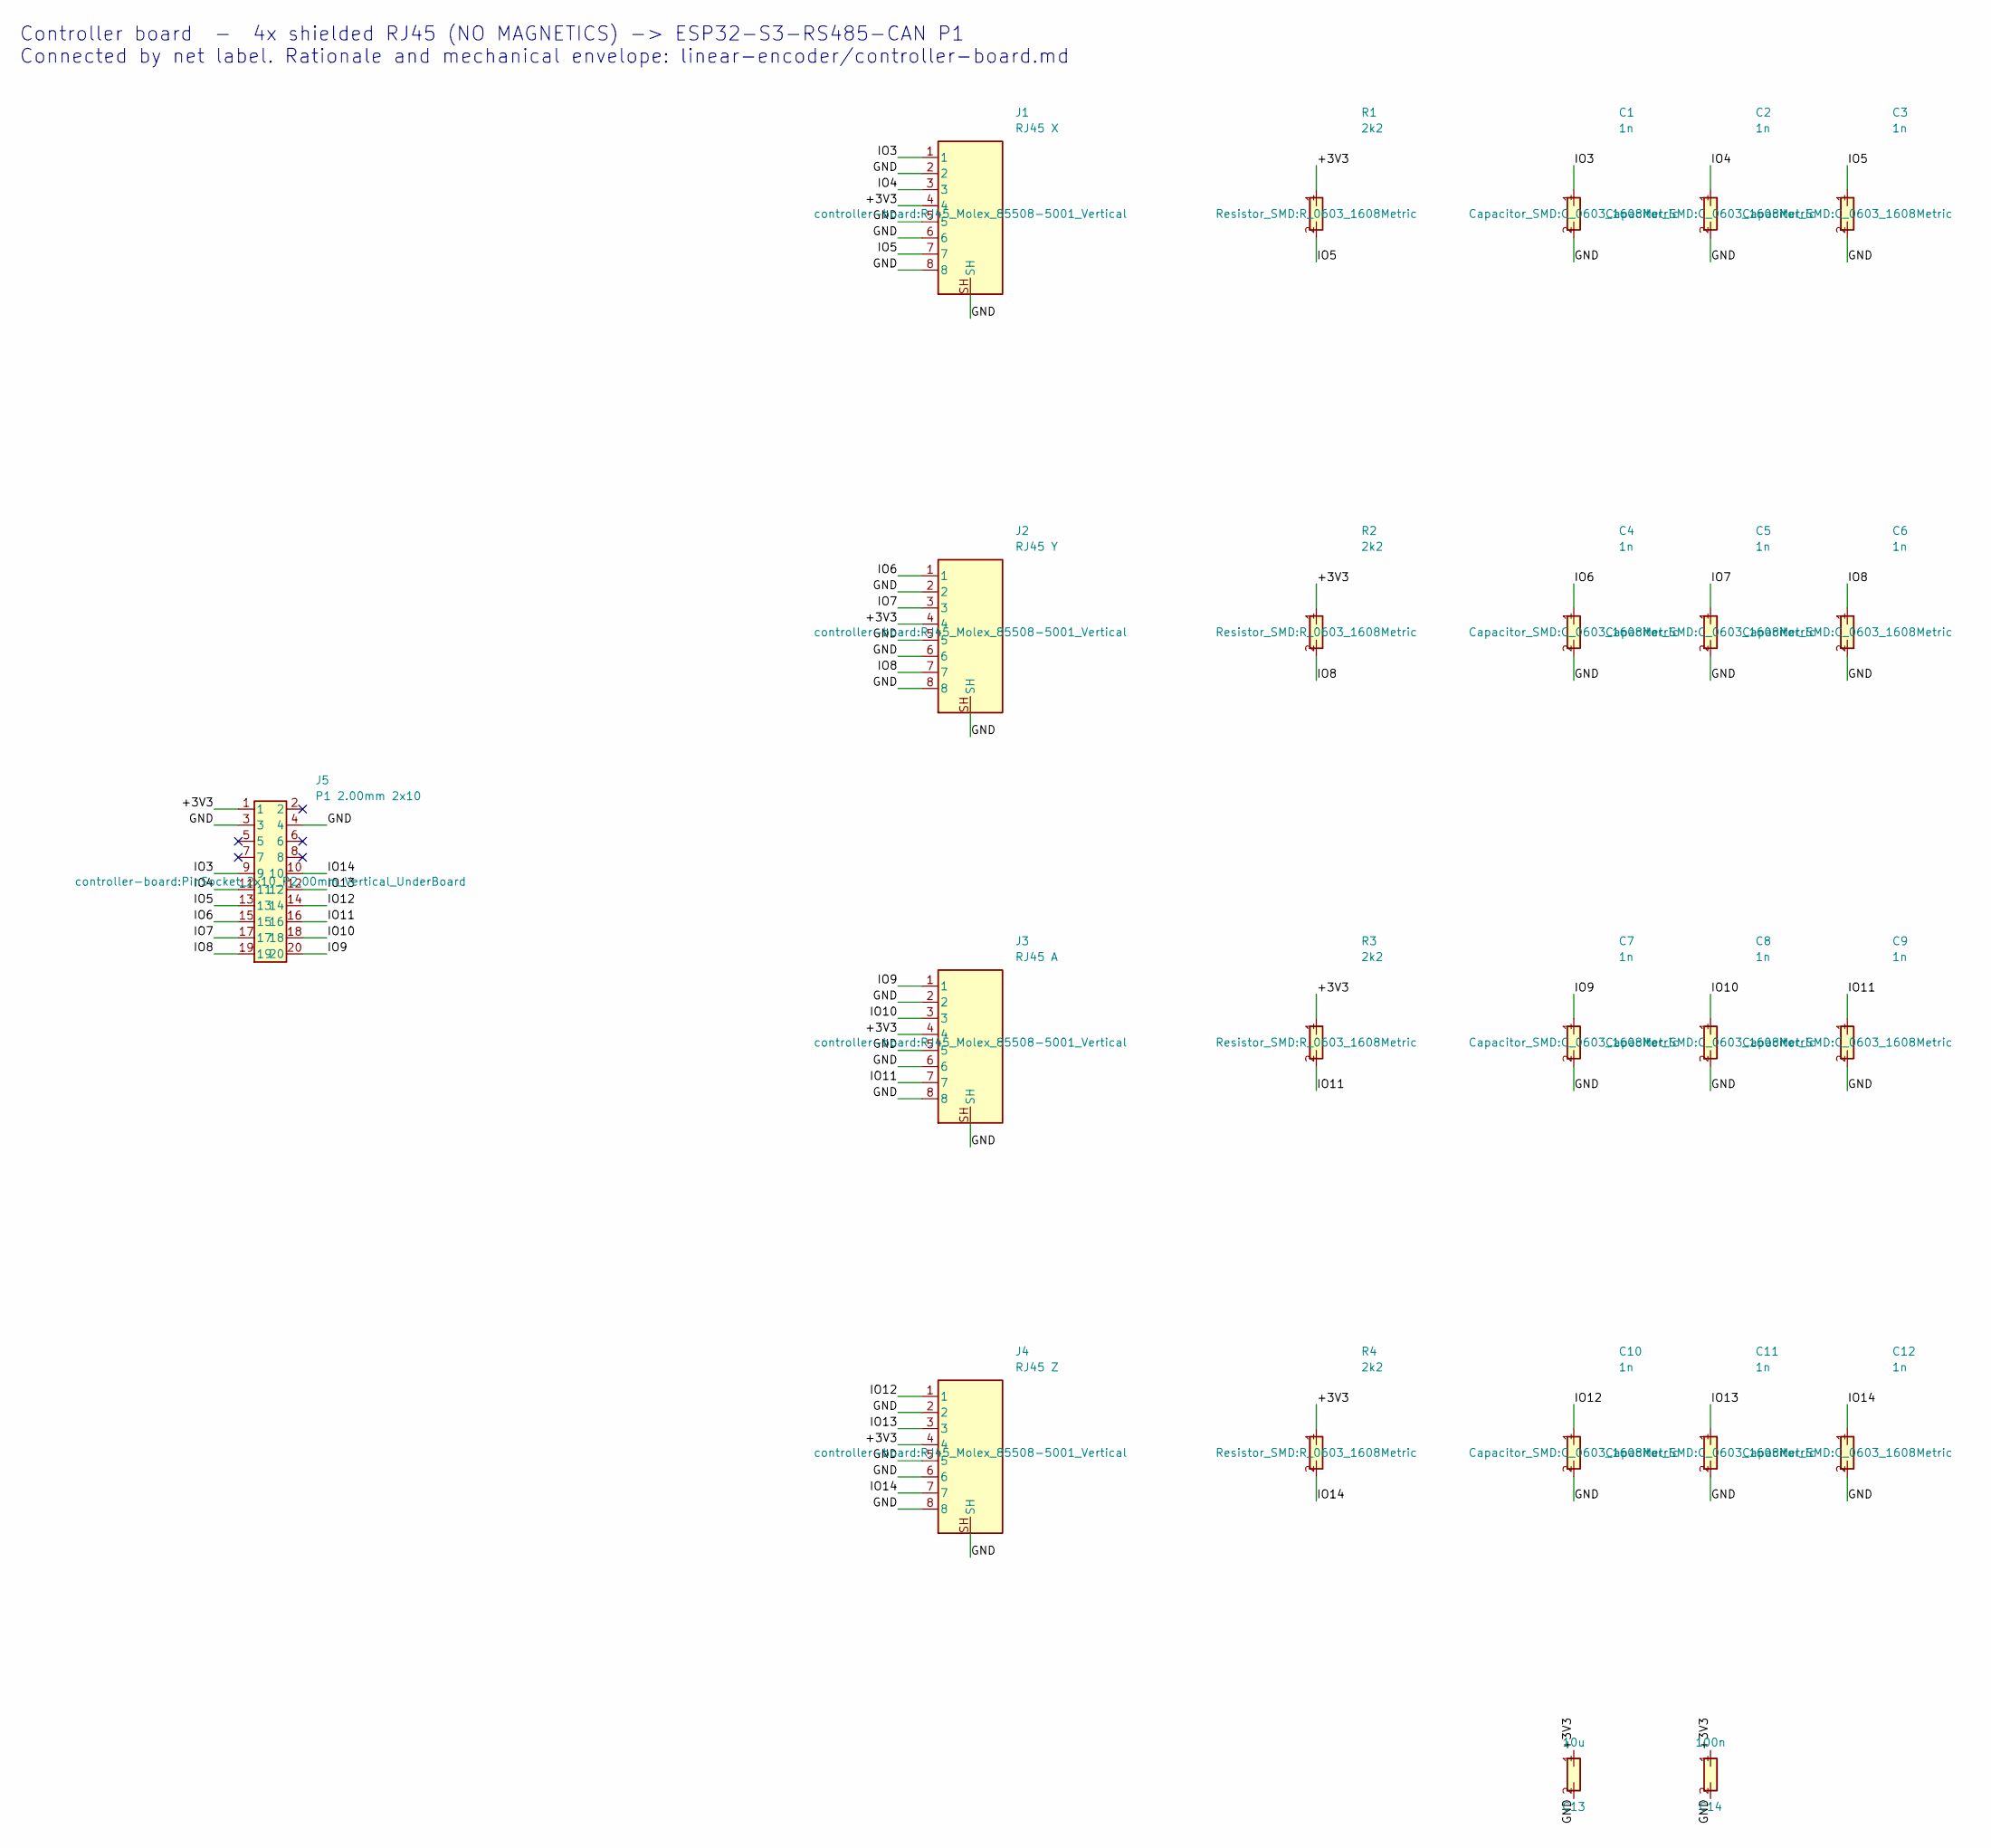
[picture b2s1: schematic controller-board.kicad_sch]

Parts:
C1, C2, C3, C4, C5, C6, C7, C8, C9, C10, C11, C12: 1n; C_0603_1608Metric
C13: 10u; C_0805_2012Metric
C14: 100n; C_0603_1608Metric
J1: RJ45 X; RJ45_Molex_85508-5001_Vertical
J2: RJ45 Y; RJ45_Molex_85508-5001_Vertical
J3: RJ45 A; RJ45_Molex_85508-5001_Vertical
J4: RJ45 Z; RJ45_Molex_85508-5001_Vertical
J5: P1 2.00mm 2x10; PinSocket_2x10_P2.00mm_Vertical_UnderBoard
R1, R2, R3, R4: 2k2; R_0603_1608Metric

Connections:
+3V3: C13.1, C14.1, J1.4, J2.4, J3.4, J4.4, J5.1, R1.1, R2.1, R3.1, R4.1
GND: C1.2, C2.2, C3.2, C4.2, C5.2, C6.2, C7.2, C8.2, C9.2, C10.2, C11.2, C12.2, C13.2, C14.2, J1.2, J1.5, J1.6, J1.8, J1.SH, J2.2, J2.5, J2.6, J2.8, J2.SH, J3.2, J3.5, J3.6, J3.8, J3.SH, J4.2, J4.5, J4.6, J4.8, J4.SH, J5.3, J5.4
IO3: C1.1, J1.1, J5.9
IO4: C2.1, J1.3, J5.11
IO5: C3.1, J1.7, J5.13, R1.2
IO6: C4.1, J2.1, J5.15
IO7: C5.1, J2.3, J5.17
IO8: C6.1, J2.7, J5.19, R2.2
IO9: C7.1, J3.1, J5.20
IO10: C8.1, J3.3, J5.18
IO11: C9.1, J3.7, J5.16, R3.2
IO12: C10.1, J4.1, J5.14
IO13: C11.1, J4.3, J5.12
IO14: C12.1, J4.7, J5.10, R4.2

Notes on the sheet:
Controller board - 4x shielded RJ45 (NO MAGNETICS) -> ESP32-S3-RS485-CAN P1 Connected by net label. Rationale and mechanical envelope: linear-encoder/controller-board.md
